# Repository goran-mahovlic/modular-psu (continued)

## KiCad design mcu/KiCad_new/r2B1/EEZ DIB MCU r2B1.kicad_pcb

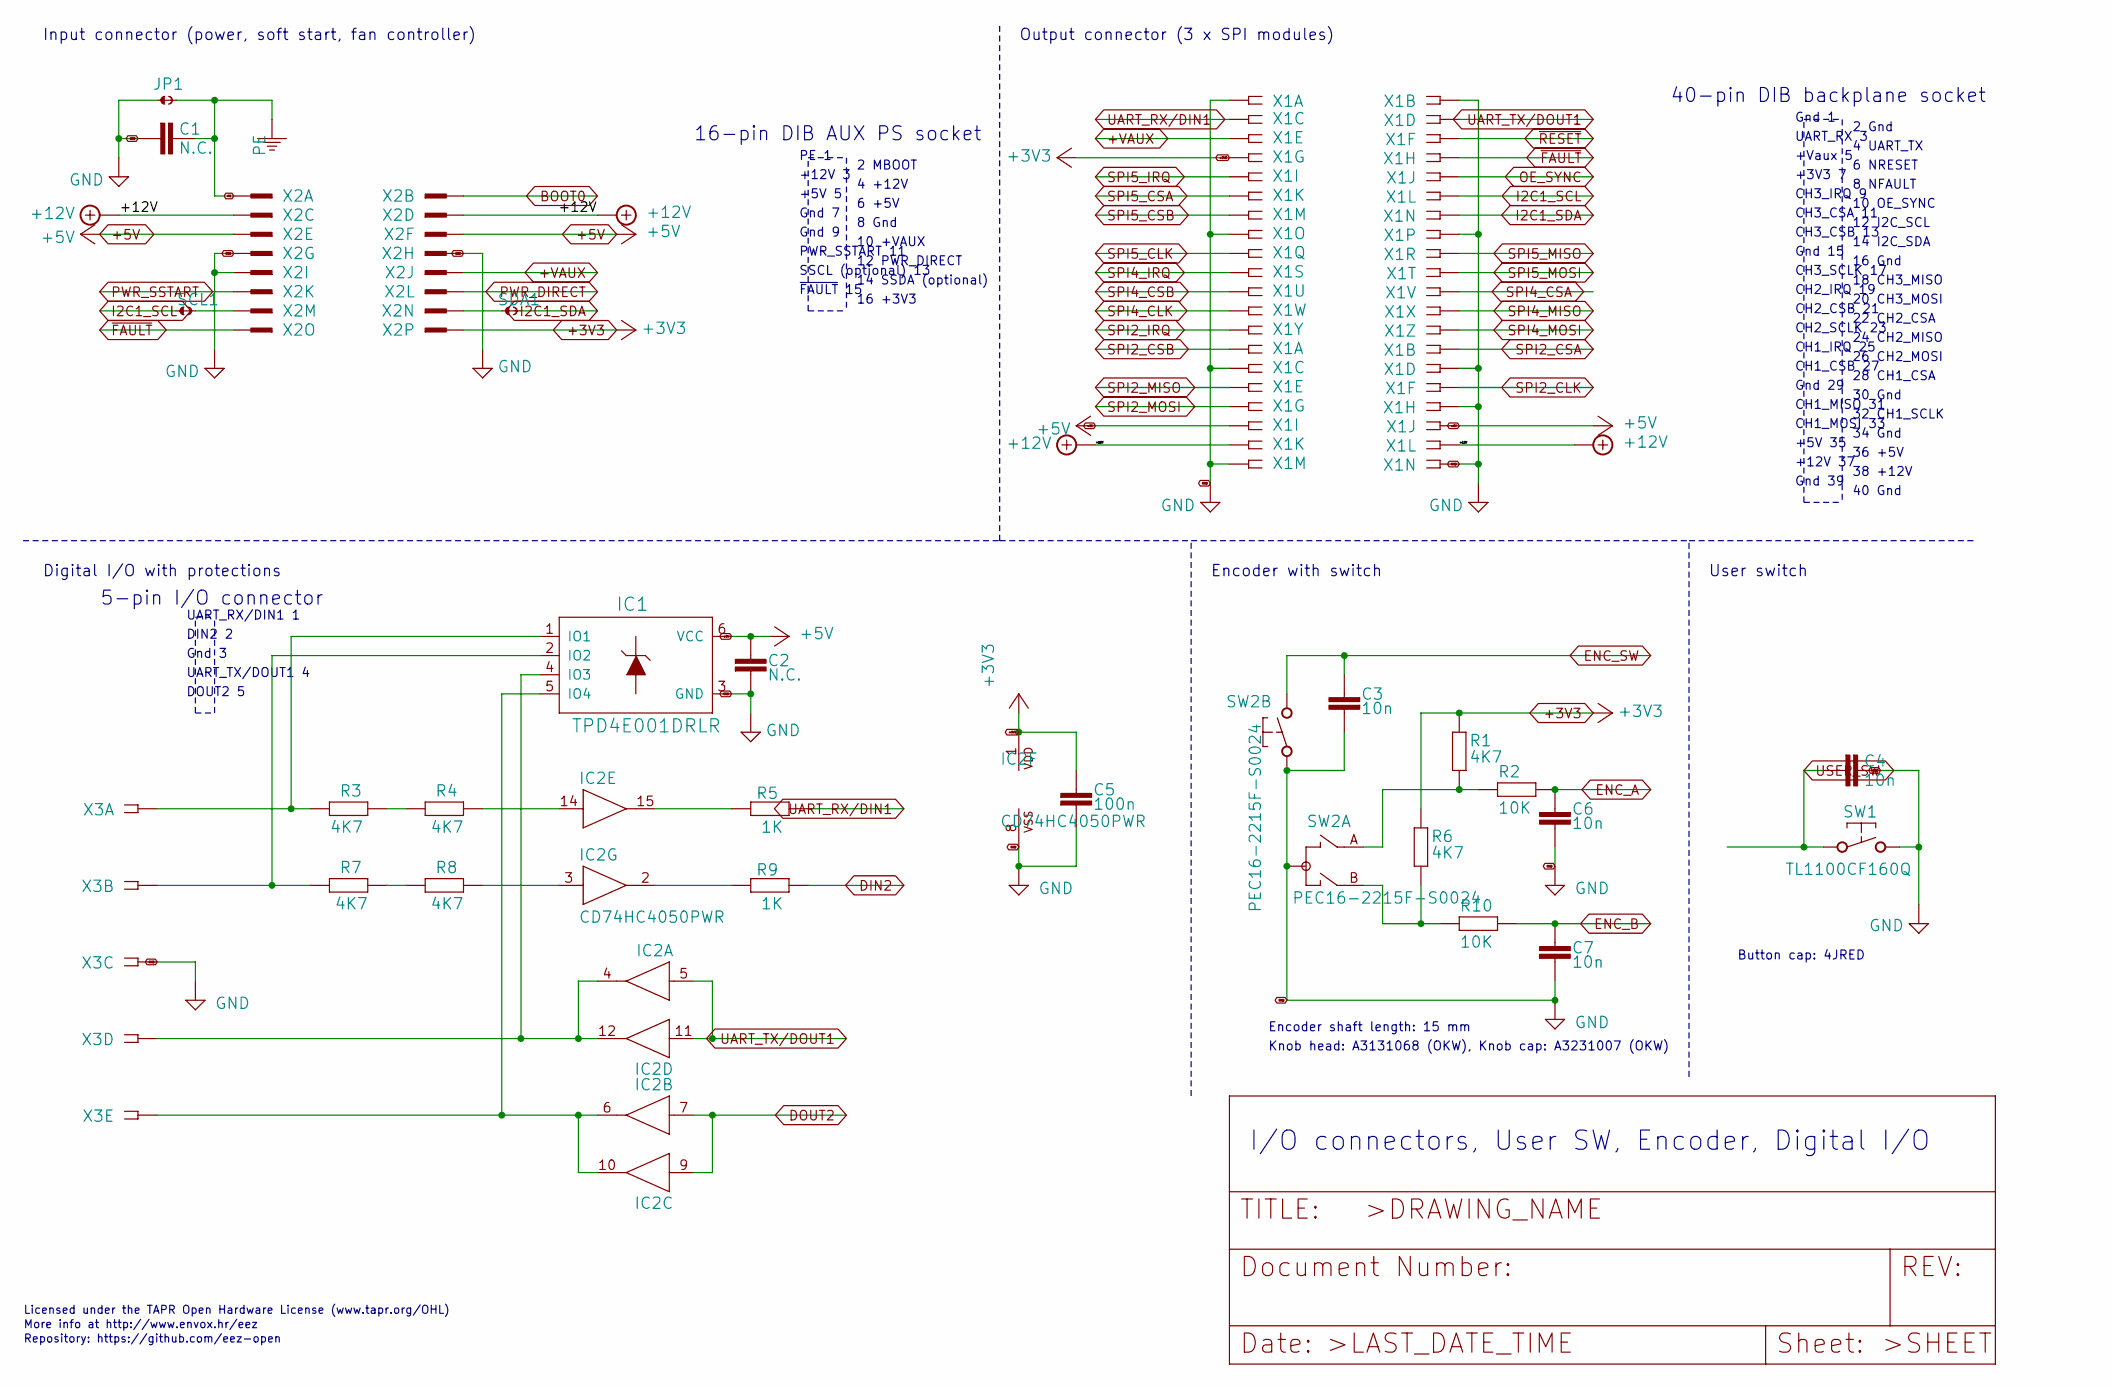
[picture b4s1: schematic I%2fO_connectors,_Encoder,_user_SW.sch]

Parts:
C1: N.C.; C0805
C2: N.C.; C0603
C3, C4, C6, C7: 10n; C0805
C5: 100n; C0603
IC1: TPD4E001DRLR; DRL6
IC2: CD74HC4050PWR; PW16
JP1: JP2-NOCUT
R1, R3, R4, R6, R7, R8: 4K7; R0805
R2, R10: 10K; R0805
R5, R9: 1K; R0805
SCL: JP2-NOCUT
SDA: JP2-NOCUT
SW1: TL1100CF160Q; TL1100C
SW2: PEC16-2215F-S0024; PEC16-2215F
X1: DS1024-2*20R0; ZL263-40DG
X2: DS1013-16SSIB1; IDC-16PIN
X3: 691322110005; MC1,5_5-G-3,5

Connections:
+3V3: C5.1, IC2.1 (VDD), R1.1, R6.1, X1.7, X2.16; also elsewhere on the board
+5V: C2.1, IC1.6 (VCC), X1.35, X1.36, X2.5, X2.6; also elsewhere on the board
+12V: X1.37, X1.38, X2.3, X2.4
+VAUX: X1.5, X2.10; also elsewhere on the board
BOOT0: X2.2; also elsewhere on the board
DIN2: R9.2; also elsewhere on the board
DOUT2: IC2.7 (I), IC2.9 (I); also elsewhere on the board
ENC_A: C6.2, R2.1; also elsewhere on the board
ENC_B: C7.1, R10.1; also elsewhere on the board
ENC_SW: C3.2, SW2.E (2); also elsewhere on the board
GND: C1.2, C2.2, C3.1, C4.1, C5.2, C6.1, C7.2, IC1.3 (GND), IC2.8 (VSS), JP1.1, SW1.2, SW2.C, SW2.D (1), SW2.GND1 (C), SW2.GND2 (C), X1.1, X1.2, X1.15, X1.16, X1.29, X1.30, X1.34, X1.39, X1.40, X2.7, X2.8, X2.9, X3.3; also elsewhere on the board
I2C1_SCL: X1.12; also elsewhere on the board
I2C1_SDA: X1.14; also elsewhere on the board
unnamed: IC1.1 (IO1), R3.1, X3.1
unnamed: IC1.2 (IO2), R7.1, X3.2
unnamed: IC1.4 (IO3), IC2.4 (O), IC2.12 (O), X3.4
unnamed: IC1.5 (IO4), IC2.6 (O), IC2.10 (O), X3.5
unnamed: IC2.2 (O), R9.1
unnamed: IC2.3 (I), R8.2
unnamed: IC2.14 (I), R4.2
unnamed: IC2.15 (O), R5.1
unnamed: R1.2, R2.2, SW2.A
unnamed: R3.2, R4.1
unnamed: R7.2, R8.1
unnamed: R6.2, R10.2, SW2.B
unnamed 199: X2.13; also elsewhere on the board
unnamed 200: X2.14; also elsewhere on the board
OE_SYNC: X1.10; also elsewhere on the board
PE: C1.1, JP1.2, X2.1; also elsewhere on the board
PWR_DIRECT: X2.12; also elsewhere on the board
PWR_SSTART: X2.11; also elsewhere on the board
SPI2_CLK: X1.32; also elsewhere on the board
SPI2_CSA: X1.28; also elsewhere on the board
SPI2_CSB: X1.27; also elsewhere on the board
SPI2_IRQ: X1.25; also elsewhere on the board
SPI2_MISO: X1.31; also elsewhere on the board
SPI2_MOSI: X1.33; also elsewhere on the board
SPI4_CLK: X1.23; also elsewhere on the board
SPI4_CSA: X1.22; also elsewhere on the board
SPI4_CSB: X1.21; also elsewhere on the board
SPI4_IRQ: X1.19; also elsewhere on the board
SPI4_MISO: X1.24; also elsewhere on the board
SPI4_MOSI: X1.26; also elsewhere on the board
SPI5_CLK: X1.17; also elsewhere on the board
SPI5_CSA: X1.11; also elsewhere on the board
SPI5_CSB: X1.13; also elsewhere on the board
SPI5_IRQ: X1.9; also elsewhere on the board
SPI5_MISO: X1.18; also elsewhere on the board
SPI5_MOSI: X1.20; also elsewhere on the board
UART_RX/DIN1: R5.2, X1.3; also elsewhere on the board
UART_TX/DOUT1: IC2.5 (I), IC2.11 (I), X1.4; also elsewhere on the board
USER_SW: C4.2, SW1.1; also elsewhere on the board
~FAULT: X1.8, X2.15; also elsewhere on the board
~RESET: X1.6; also elsewhere on the board

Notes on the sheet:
Licensed under the TAPR Open Hardware License (www.tapr.org/OHL)
Repository: https://github.com/eez-open
More info at http://www.envox.hr/eez
Encoder shaft length: 15 mm
Knob head: A3131068 (OKW), Knob cap: A3231007 (OKW)
I/O connectors, User SW, Encoder, Digital I/O
2 MBOOT
Gnd 7
6 +5V
8 Gnd
10 +VAUX
4 +12V
+12V 3
PE 1
16-pin DIB AUX PS socket
+5V 5
Gnd 9
SSCL (optional) 13
12 PWR_DIRECT
PWR_SSTART 11
14 SSDA (optional)
~FAULT~ 15
16 +3V3
Digital I/O with protections
Encoder with switch
User switch
Input connector (power, soft start, fan controller)
Output connector (3 x SPI modules)
Button cap: 4JRED
2 Gnd
+3V3 7
6 NRESET
8 NFAULT
10 OE_SYNC
4 UART_TX
UART_RX 3
Gnd 1
40-pin DIB backplane socket
+Vaux 5
CH3_IRQ 9

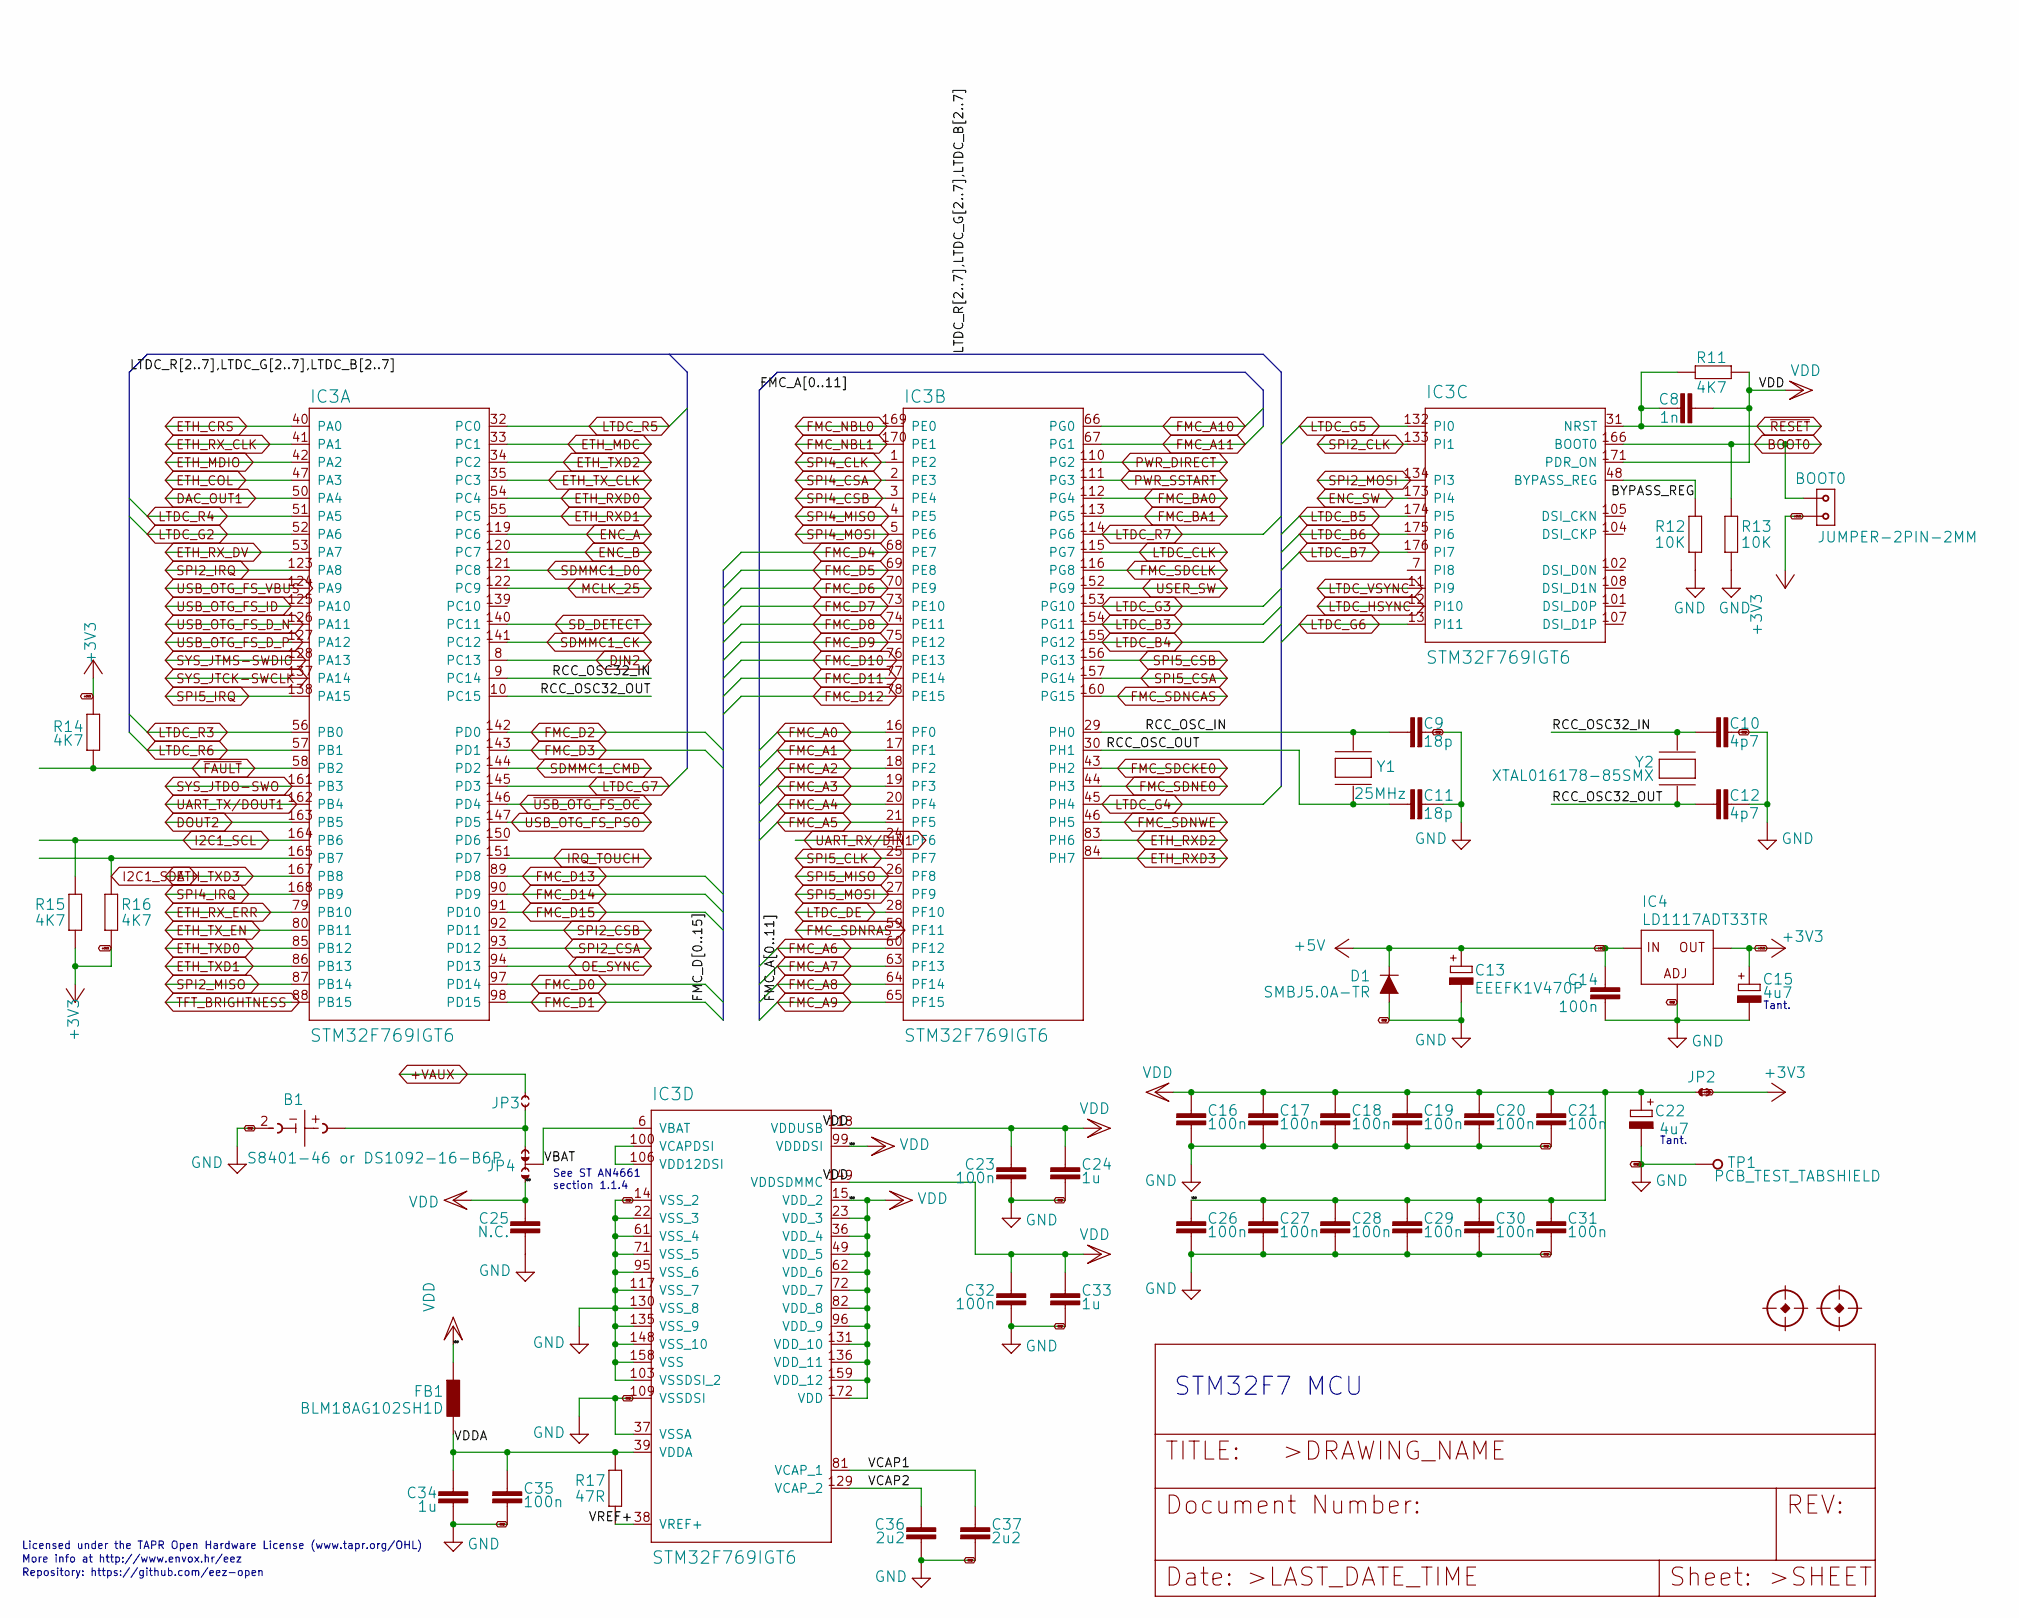
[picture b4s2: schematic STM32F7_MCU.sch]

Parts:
B1: S8401-46 or DS1092-16-B6P; S8401-46
BOOT0: JUMPER-2PIN-2MM; 2MM-2
C8: 1n; C0805
C9, C11: 18p; C0603
C10, C12: 4p7; C0603
C13: EEEFK1V470P; CAPAE660X610N
C14, C16, C17, C18, C19, C20, C21, C23, C26, C27, C28, C29, C30, C31, C32, C35: 100n; C0603
C15, C22: 4u7; EC1206
C24, C33, C34: 1u; C0805
C25: N.C.; C0603
C36, C37: 2u2; C0805
D1: SMBJ5.0A-TR; DO214AA
FB1: BLM18AG102SH1D; BEAD0603
FM1, FM2: FIDUCIAL
IC3: STM32F769IGT6; LQFP-176_24X24MM
IC4: LD1117ADT33TR; DPACK
JP2: JP2-NOCUT
JP3: JP2-CUT
JP4: JP3-CUT
R11, R14, R15, R16: 4K7; R0805
R12, R13: 10K; R0805
R17: 47R; R0805
TP1: PCB_TEST_TABSHIELD; PCB_SHIELD_TAB
Y1: 25MHz; HC-49_4H
Y2: XTAL016178-85SMX; 85SMX

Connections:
+3V3: BOOT0.2, C15.+, IC4.4 (OUT), JP2.2, R14.1, R15.1, R16.1; also elsewhere on the board
+5V: C13.1 (+), C14.1, D1.C, IC4.3 (IN); also elsewhere on the board
+VAUX: JP3.2; also elsewhere on the board
/STM32F7 MCU/BYPASS_REG: IC3.48 (BYPASS_REG), R12.2
/STM32F7 MCU/RCC_OSC32_IN: C10.1, IC3.9 (PC14), Y2.1
/STM32F7 MCU/RCC_OSC32_OUT: C12.1, IC3.10 (PC15), Y2.4 (2)
/STM32F7 MCU/RCC_OSC_IN: C9.2, IC3.29 (PH0), Y1.2
/STM32F7 MCU/RCC_OSC_OUT: C11.2, IC3.30 (PH1), Y1.1
/STM32F7 MCU/VBAT: IC3.6 (VBAT), JP4.COM
/STM32F7 MCU/VCAP1: C37.1, IC3.81 (VCAP_1)
/STM32F7 MCU/VCAP2: C36.1, IC3.129 (VCAP_2)
/STM32F7 MCU/VDDA: C34.1, C35.1, FB1.P$2 (2), IC3.39 (VDDA), R17.2
/STM32F7 MCU/VREF+: IC3.38 (VREF+), R17.1
BOOT0: BOOT0.1, IC3.166 (BOOT0), R13.2; also elsewhere on the board
DAC_OUT1: IC3.50 (PA4); also elsewhere on the board
DIN2: IC3.8 (PC13); also elsewhere on the board
DOUT2: IC3.163 (PB5); also elsewhere on the board
ENC_A: IC3.119 (PC6); also elsewhere on the board
ENC_B: IC3.120 (PC7); also elsewhere on the board
ENC_SW: IC3.173 (PI4); also elsewhere on the board
ETH_COL: IC3.47 (PA3); also elsewhere on the board
ETH_CRS: IC3.40 (PA0); also elsewhere on the board
ETH_MDC: IC3.33 (PC1); also elsewhere on the board
ETH_MDIO: IC3.42 (PA2); also elsewhere on the board
ETH_RXD0: IC3.54 (PC4); also elsewhere on the board
ETH_RXD1: IC3.55 (PC5); also elsewhere on the board
ETH_RXD2: IC3.83 (PH6); also elsewhere on the board
ETH_RXD3: IC3.84 (PH7); also elsewhere on the board
ETH_RX_CLK: IC3.41 (PA1); also elsewhere on the board
ETH_RX_DV: IC3.53 (PA7); also elsewhere on the board
ETH_RX_ERR: IC3.79 (PB10); also elsewhere on the board
ETH_TXD0: IC3.85 (PB12); also elsewhere on the board
ETH_TXD1: IC3.86 (PB13); also elsewhere on the board
ETH_TXD2: IC3.34 (PC2); also elsewhere on the board
ETH_TXD3: IC3.167 (PB8); also elsewhere on the board
ETH_TX_CLK: IC3.35 (PC3); also elsewhere on the board
ETH_TX_EN: IC3.80 (PB11); also elsewhere on the board
FMC_A0: IC3.16 (PF0); also elsewhere on the board
FMC_A1: IC3.17 (PF1); also elsewhere on the board
FMC_A2: IC3.18 (PF2); also elsewhere on the board
FMC_A3: IC3.19 (PF3); also elsewhere on the board
FMC_A4: IC3.20 (PF4); also elsewhere on the board
FMC_A5: IC3.21 (PF5); also elsewhere on the board
FMC_A6: IC3.60 (PF12); also elsewhere on the board
FMC_A7: IC3.63 (PF13); also elsewhere on the board
FMC_A8: IC3.64 (PF14); also elsewhere on the board
FMC_A9: IC3.65 (PF15); also elsewhere on the board
FMC_A10: IC3.66 (PG0); also elsewhere on the board
FMC_A11: IC3.67 (PG1); also elsewhere on the board
FMC_BA0: IC3.112 (PG4); also elsewhere on the board
FMC_BA1: IC3.113 (PG5); also elsewhere on the board
FMC_D0: IC3.97 (PD14); also elsewhere on the board
FMC_D1: IC3.98 (PD15); also elsewhere on the board
FMC_D2: IC3.142 (PD0); also elsewhere on the board
FMC_D3: IC3.143 (PD1); also elsewhere on the board
FMC_D4: IC3.68 (PE7); also elsewhere on the board
FMC_D5: IC3.69 (PE8); also elsewhere on the board
FMC_D6: IC3.70 (PE9); also elsewhere on the board
FMC_D7: IC3.73 (PE10); also elsewhere on the board
FMC_D8: IC3.74 (PE11); also elsewhere on the board
FMC_D9: IC3.75 (PE12); also elsewhere on the board
FMC_D10: IC3.76 (PE13); also elsewhere on the board
FMC_D11: IC3.77 (PE14); also elsewhere on the board
FMC_D12: IC3.78 (PE15); also elsewhere on the board
FMC_D13: IC3.89 (PD8); also elsewhere on the board
FMC_D14: IC3.90 (PD9); also elsewhere on the board
FMC_D15: IC3.91 (PD10); also elsewhere on the board
FMC_NBL0: IC3.169 (PE0); also elsewhere on the board
FMC_NBL1: IC3.170 (PE1); also elsewhere on the board
FMC_SDCKE0: IC3.43 (PH2); also elsewhere on the board
FMC_SDCLK: IC3.116 (PG8); also elsewhere on the board
FMC_SDNCAS: IC3.160 (PG15); also elsewhere on the board
FMC_SDNE0: IC3.44 (PH3); also elsewhere on the board
FMC_SDNRAS: IC3.59 (PF11); also elsewhere on the board
FMC_SDNWE: IC3.46 (PH5); also elsewhere on the board
GND: B1.2 (-), C9.1, C10.2, C11.1, C12.2, C13.2 (-), C14.2, C15.-, C16.2, C17.2, C18.2, C19.2, C20.2, C21.2, C22.-, C23.2, C24.2, C25.2, C26.2, C27.2, C28.2, C29.2, C30.2, C31.2, C32.2, C33.2, C34.2, C35.2, C36.2, C37.2, D1.A, IC3.14 (VSS_2), IC3.22 (VSS_3), IC3.37 (VSSA), IC3.61 (VSS_4), IC3.71 (VSS_5), IC3.95 (VSS_6), IC3.103 (VSSDSI_2), IC3.109 (VSSDSI), IC3.117 (VSS_7), IC3.130 (VSS_8), IC3.135 (VSS_9), IC3.148 (VSS_10), IC3.158 (VSS), IC4.1 (ADJ), R12.1, R13.1, TP1.1; also elsewhere on the board
I2C1_SCL: IC3.164 (PB6), R15.2; also elsewhere on the board
I2C1_SDA: IC3.165 (PB7), R16.2; also elsewhere on the board
IRQ_TOUCH: IC3.151 (PD7); also elsewhere on the board
LTDC_B3: IC3.154 (PG11); also elsewhere on the board
LTDC_B4: IC3.155 (PG12); also elsewhere on the board
LTDC_B5: IC3.174 (PI5); also elsewhere on the board
LTDC_B6: IC3.175 (PI6); also elsewhere on the board
LTDC_B7: IC3.176 (PI7); also elsewhere on the board
LTDC_CLK: IC3.115 (PG7); also elsewhere on the board
LTDC_DE: IC3.28 (PF10); also elsewhere on the board
LTDC_G2: IC3.52 (PA6); also elsewhere on the board
LTDC_G3: IC3.153 (PG10); also elsewhere on the board
LTDC_G4: IC3.45 (PH4); also elsewhere on the board
LTDC_G5: IC3.132 (PI0); also elsewhere on the board
LTDC_G6: IC3.13 (PI11); also elsewhere on the board
LTDC_G7: IC3.145 (PD3); also elsewhere on the board
LTDC_HSYNC: IC3.12 (PI10); also elsewhere on the board
LTDC_R3: IC3.56 (PB0); also elsewhere on the board
LTDC_R4: IC3.51 (PA5); also elsewhere on the board
LTDC_R5: IC3.32 (PC0); also elsewhere on the board
LTDC_R6: IC3.57 (PB1); also elsewhere on the board
LTDC_R7: IC3.114 (PG6); also elsewhere on the board
LTDC_VSYNC: IC3.11 (PI9); also elsewhere on the board
MCLK_25: IC3.122 (PC9); also elsewhere on the board
unnamed: B1.1 (+), B1.3 (+), JP3.1, JP4.NC
unnamed: IC3.100 (VCAPDSI), IC3.106 (VDD12DSI)
OE_SYNC: IC3.94 (PD13); also elsewhere on the board
PWR_DIRECT: IC3.110 (PG2); also elsewhere on the board
PWR_SSTART: IC3.111 (PG3); also elsewhere on the board
SDMMC1_CK: IC3.141 (PC12); also elsewhere on the board
SDMMC1_CMD: IC3.144 (PD2); also elsewhere on the board
SDMMC1_D0: IC3.121 (PC8); also elsewhere on the board
SD_DETECT: IC3.140 (PC11); also elsewhere on the board
SPI2_CLK: IC3.133 (PI1); also elsewhere on the board
SPI2_CSA: IC3.93 (PD12); also elsewhere on the board
SPI2_CSB: IC3.92 (PD11); also elsewhere on the board
SPI2_IRQ: IC3.123 (PA8); also elsewhere on the board
SPI2_MISO: IC3.87 (PB14); also elsewhere on the board
SPI2_MOSI: IC3.134 (PI3); also elsewhere on the board
SPI4_CLK: IC3.1 (PE2); also elsewhere on the board
SPI4_CSA: IC3.2 (PE3); also elsewhere on the board
SPI4_CSB: IC3.3 (PE4); also elsewhere on the board
SPI4_IRQ: IC3.168 (PB9); also elsewhere on the board
SPI4_MISO: IC3.4 (PE5); also elsewhere on the board
SPI4_MOSI: IC3.5 (PE6); also elsewhere on the board
SPI5_CLK: IC3.25 (PF7); also elsewhere on the board
SPI5_CSA: IC3.157 (PG14); also elsewhere on the board
SPI5_CSB: IC3.156 (PG13); also elsewhere on the board
SPI5_IRQ: IC3.138 (PA15); also elsewhere on the board
SPI5_MISO: IC3.26 (PF8); also elsewhere on the board
SPI5_MOSI: IC3.27 (PF9); also elsewhere on the board
SYS_JTCK-SWCLK: IC3.137 (PA14); also elsewhere on the board
SYS_JTDO-SWO: IC3.161 (PB3); also elsewhere on the board
SYS_JTMS-SWDIO: IC3.128 (PA13); also elsewhere on the board
TFT_BRIGHTNESS: IC3.88 (PB15); also elsewhere on the board
UART_RX/DIN1: IC3.24 (PF6); also elsewhere on the board
UART_TX/DOUT1: IC3.162 (PB4); also elsewhere on the board
USB_OTG_FS_D_N: IC3.126 (PA11); also elsewhere on the board
USB_OTG_FS_D_P: IC3.127 (PA12); also elsewhere on the board
USB_OTG_FS_ID: IC3.125 (PA10); also elsewhere on the board
USB_OTG_FS_PSO: IC3.147 (PD5); also elsewhere on the board
USB_OTG_FS_VBUS: IC3.124 (PA9); also elsewhere on the board
USER_SW: IC3.152 (PG9); also elsewhere on the board
VDD: C8.2, C16.1, C17.1, C18.1, C19.1, C20.1, C21.1, C22.+, C23.1, C24.1, C25.1, C26.1, C27.1, C28.1, C29.1, C30.1, C31.1, C32.1, C33.1, FB1.P$1 (1), IC3.15 (VDD_2), IC3.23 (VDD_3), IC3.36 (VDD_4), IC3.49 (VDD_5), IC3.62 (VDD_6), IC3.72 (VDD_7), IC3.82 (VDD_8), IC3.96 (VDD_9), IC3.99 (VDDDSI), IC3.118 (VDDUSB), IC3.131 (VDD_10), IC3.136 (VDD_11), IC3.149 (VDDSDMMC), IC3.159 (VDD_12), IC3.171 (PDR_ON), IC3.172 (VDD), JP2.1, JP4.NO, R11.1
~FAULT: IC3.58 (PB2), R14.2; also elsewhere on the board
~RESET: C8.1, IC3.31 (NRST), R11.2; also elsewhere on the board
~USB_OTG_FS_OC: IC3.146 (PD4); also elsewhere on the board

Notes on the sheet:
Licensed under the TAPR Open Hardware License (www.tapr.org/OHL)
Repository: https://github.com/eez-open
More info at http://www.envox.hr/eez
Tant.
See ST AN4661 section 1.1.4
STM32F7 MCU

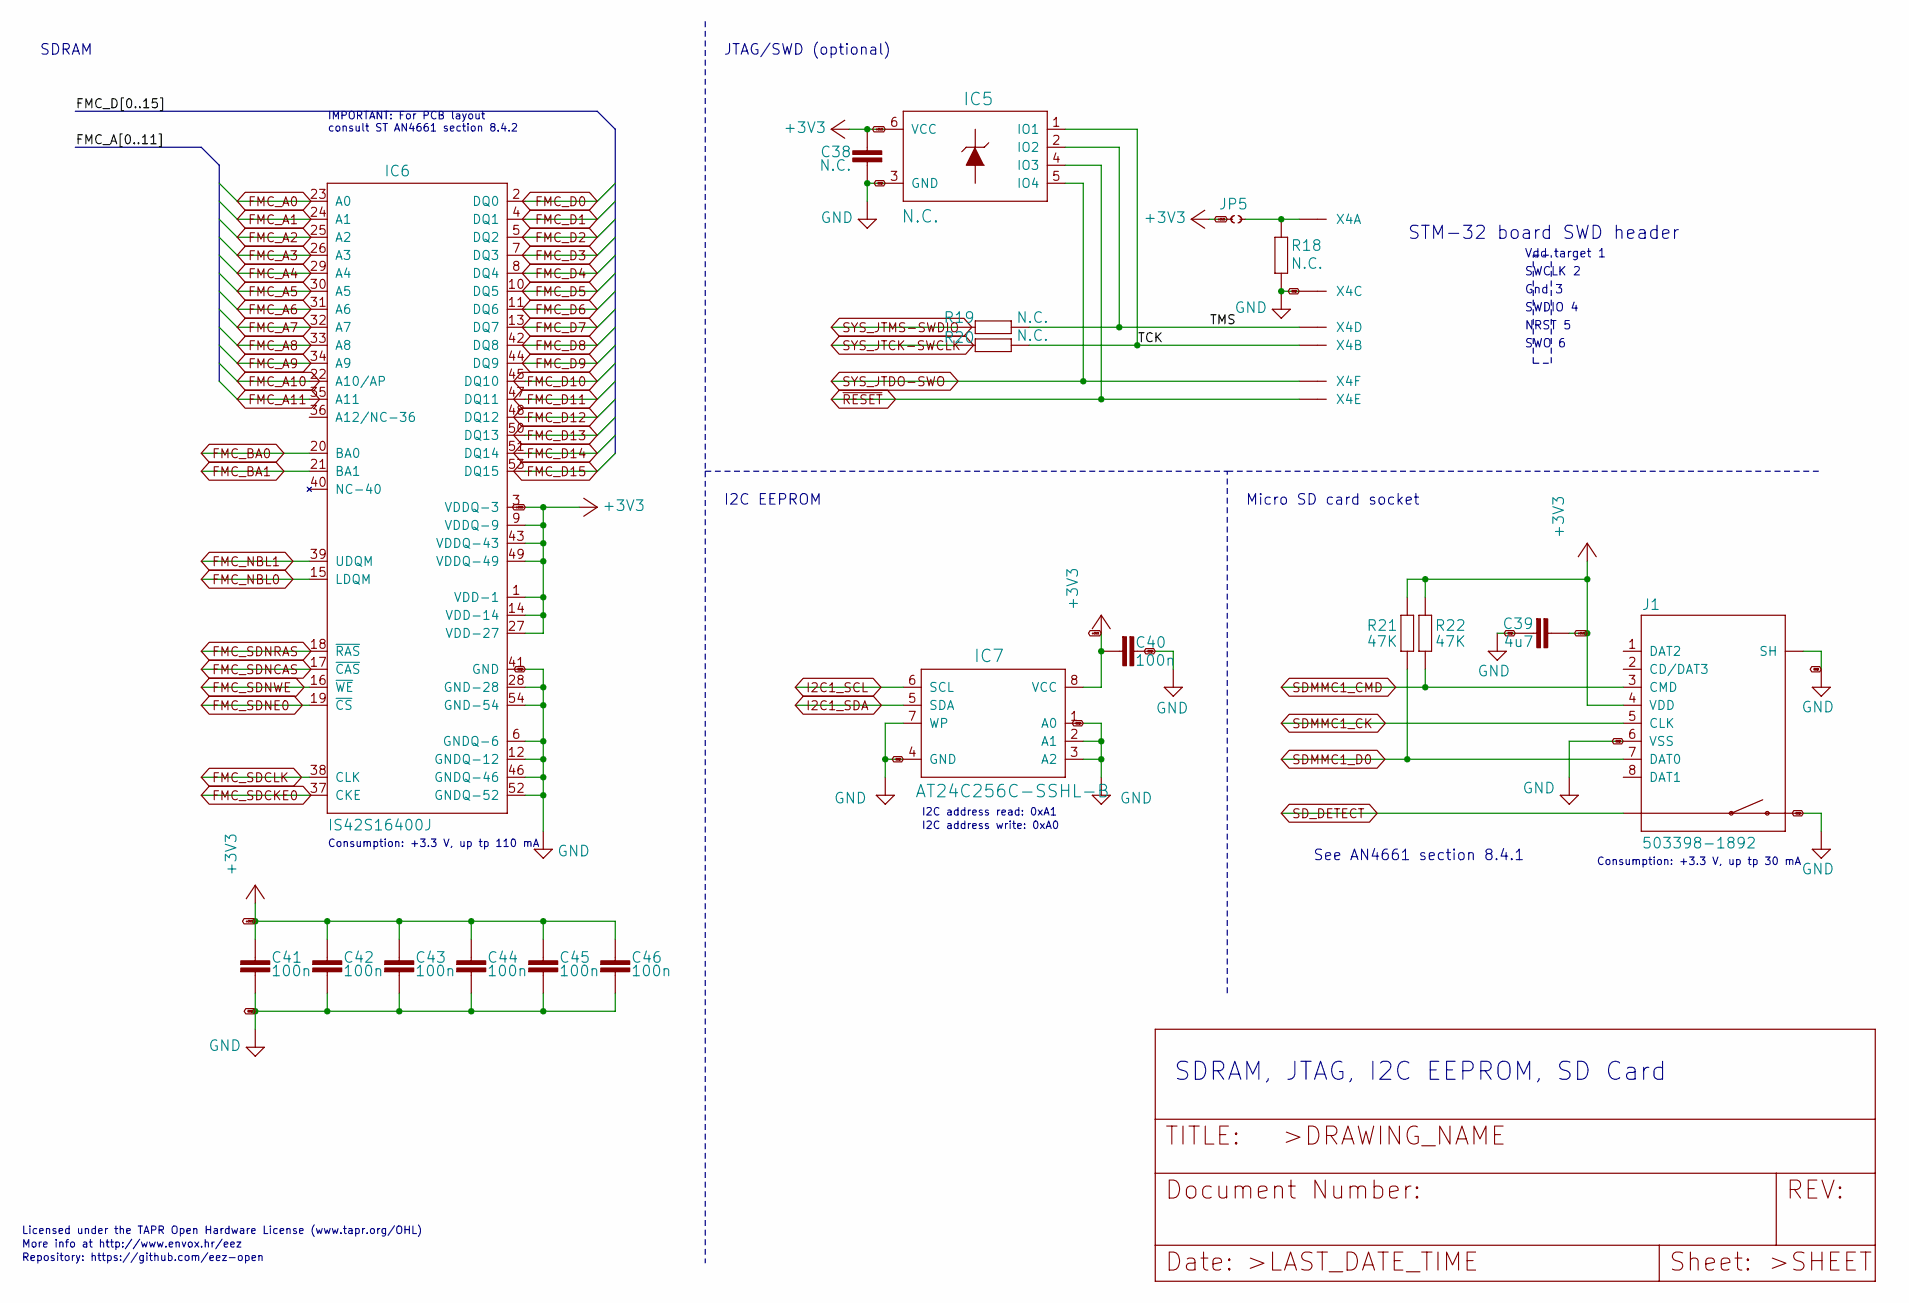
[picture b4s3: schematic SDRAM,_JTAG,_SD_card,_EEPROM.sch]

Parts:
C38: N.C.; C0603
C39: 4u7; C1206
C40, C41, C42, C43, C44, C45, C46: 100n; C0603
IC5: N.C.; DRL6
IC6: IS42S16400J; TSOPII-54
IC7: AT24C256C-SSHL-B; SOIC127P600X173-8N
J1: 503398-1892; 5033981892
JP5: JP2-CUT
R18, R19, R20: N.C.; R0805
R21, R22: 47K; R0805
X4: N.C.; 22-23-2061

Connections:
+3V3: C38.1, C39.1, C40.2, C41.1, C42.1, C43.1, C44.1, C45.1, C46.1, IC5.6 (VCC), IC6.1 (VDD-1), IC6.3 (VDDQ-3), IC6.9 (VDDQ-9), IC6.14 (VDD-14), IC6.27 (VDD-27), IC6.43 (VDDQ-43), IC6.49 (VDDQ-49), IC7.8 (VCC), J1.4 (VDD), JP5.1, R21.1, R22.1; also elsewhere on the board
/SDRAM, JTAG, SD card, EEPROM/TCK: IC5.1 (IO1), R20.2, X4.2
/SDRAM, JTAG, SD card, EEPROM/TMS: IC5.2 (IO2), R19.2, X4.4
FMC_A0: IC6.23 (A0); also elsewhere on the board
FMC_A1: IC6.24 (A1); also elsewhere on the board
FMC_A2: IC6.25 (A2); also elsewhere on the board
FMC_A3: IC6.26 (A3); also elsewhere on the board
FMC_A4: IC6.29 (A4); also elsewhere on the board
FMC_A5: IC6.30 (A5); also elsewhere on the board
FMC_A6: IC6.31 (A6); also elsewhere on the board
FMC_A7: IC6.32 (A7); also elsewhere on the board
FMC_A8: IC6.33 (A8); also elsewhere on the board
FMC_A9: IC6.34 (A9); also elsewhere on the board
FMC_A10: IC6.22 (A10/AP); also elsewhere on the board
FMC_A11: IC6.35 (A11); also elsewhere on the board
FMC_BA0: IC6.20 (BA0); also elsewhere on the board
FMC_BA1: IC6.21 (BA1); also elsewhere on the board
FMC_D0: IC6.2 (DQ0); also elsewhere on the board
FMC_D1: IC6.4 (DQ1); also elsewhere on the board
FMC_D2: IC6.5 (DQ2); also elsewhere on the board
FMC_D3: IC6.7 (DQ3); also elsewhere on the board
FMC_D4: IC6.8 (DQ4); also elsewhere on the board
FMC_D5: IC6.10 (DQ5); also elsewhere on the board
FMC_D6: IC6.11 (DQ6); also elsewhere on the board
FMC_D7: IC6.13 (DQ7); also elsewhere on the board
FMC_D8: IC6.42 (DQ8); also elsewhere on the board
FMC_D9: IC6.44 (DQ9); also elsewhere on the board
FMC_D10: IC6.45 (DQ10); also elsewhere on the board
FMC_D11: IC6.47 (DQ11); also elsewhere on the board
FMC_D12: IC6.48 (DQ12); also elsewhere on the board
FMC_D13: IC6.50 (DQ13); also elsewhere on the board
FMC_D14: IC6.51 (DQ14); also elsewhere on the board
FMC_D15: IC6.53 (DQ15); also elsewhere on the board
FMC_NBL0: IC6.15 (LDQM); also elsewhere on the board
FMC_NBL1: IC6.39 (UDQM); also elsewhere on the board
FMC_SDCKE0: IC6.37 (CKE); also elsewhere on the board
FMC_SDCLK: IC6.38 (CLK); also elsewhere on the board
FMC_SDNCAS: IC6.17 (~CAS); also elsewhere on the board
FMC_SDNE0: IC6.19 (~CS); also elsewhere on the board
FMC_SDNRAS: IC6.18 (~RAS); also elsewhere on the board
FMC_SDNWE: IC6.16 (~WE); also elsewhere on the board
GND: C38.2, C39.2, C40.1, C41.2, C42.2, C43.2, C44.2, C45.2, C46.2, IC5.3 (GND), IC6.6 (GNDQ-6), IC6.12 (GNDQ-12), IC6.28 (GND-28), IC6.41 (GND), IC6.46 (GNDQ-46), IC6.52 (GNDQ-52), IC6.54 (GND-54), IC7.1 (A0), IC7.2 (A1), IC7.3 (A2), IC7.4 (GND), IC7.7 (WP), J1.6 (VSS), J1.S (SH), J1.S1 (SH), J1.S2 (SH), J1.SW2, R18.1, X4.3; also elsewhere on the board
I2C1_SCL: IC7.6 (SCL); also elsewhere on the board
I2C1_SDA: IC7.5 (SDA); also elsewhere on the board
unnamed: JP5.2, R18.2, X4.1
SDMMC1_CK: J1.5 (CLK); also elsewhere on the board
SDMMC1_CMD: J1.3 (CMD), R22.2; also elsewhere on the board
SDMMC1_D0: J1.7 (DAT0), R21.2; also elsewhere on the board
SD_DETECT: J1.SW1; also elsewhere on the board
SYS_JTCK-SWCLK: R20.1; also elsewhere on the board
SYS_JTDO-SWO: IC5.5 (IO4), X4.6; also elsewhere on the board
SYS_JTMS-SWDIO: R19.1; also elsewhere on the board
~RESET: IC5.4 (IO3), X4.5; also elsewhere on the board

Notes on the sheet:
SDRAM, JTAG, I2C EEPROM, SD Card
Consumption: +3.3 V, up tp 30 mA
Licensed under the TAPR Open Hardware License (www.tapr.org/OHL)
Repository: https://github.com/eez-open
More info at http://www.envox.hr/eez
Consumption: +3.3 V, up tp 110 mA
I2C address read: 0xA1
I2C address write: 0xA0
I2C EEPROM
IMPORTANT: For PCB layout consult ST AN4661 section 8.4.2
See AN4661 section 8.4.1
Micro SD card socket
SWDIO 4
SWCLK 2
Vdd target 1
STM-32 board SWD header
Gnd 3
NRST 5
SWO 6
JTAG/SWD (optional)
SDRAM
